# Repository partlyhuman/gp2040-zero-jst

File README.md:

You can quick-order this board at [OSHPark](https://oshpark.com/shared_projects/QktXrqFz).

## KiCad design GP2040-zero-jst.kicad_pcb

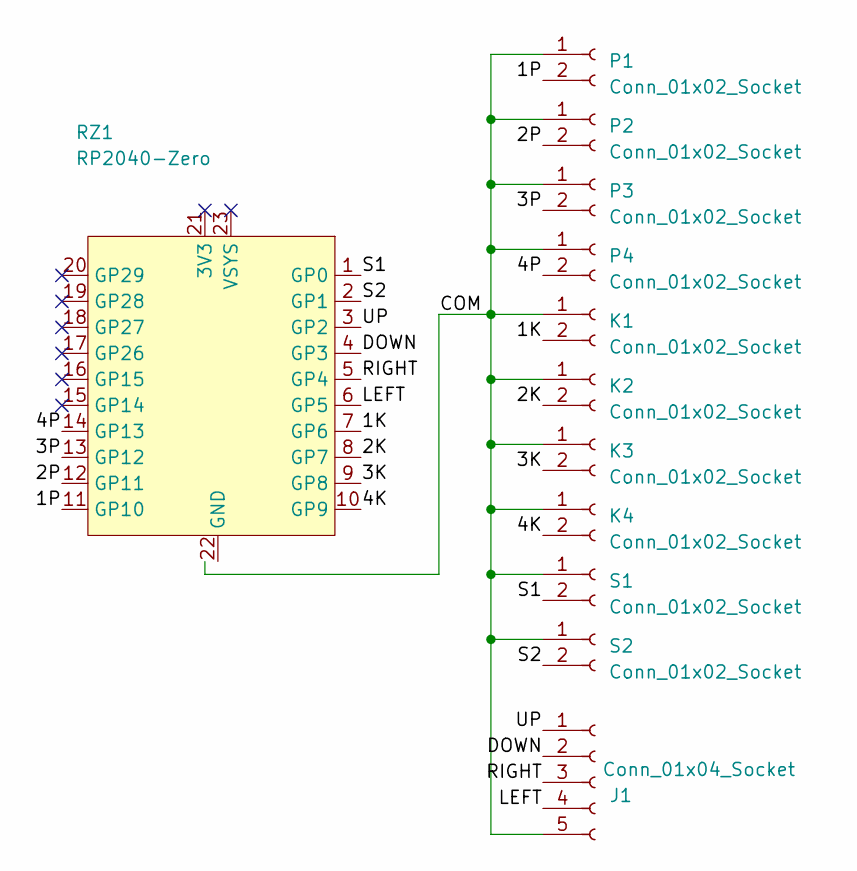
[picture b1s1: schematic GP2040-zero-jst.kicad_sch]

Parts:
J1: Conn_01x04_Socket; JST_XH_B5B-XH-A_1x05_P2.50mm_Vertical
K1, K2, K3, K4: Conn_01x02_Socket; JST_XH_B2B-XH-A_1x02_P2.50mm_Vertical
P1, P2, P3, P4: Conn_01x02_Socket; JST_XH_B2B-XH-A_1x02_P2.50mm_Vertical
RZ1: RP2040-Zero
S1, S2: Conn_01x02_Socket; JST_XH_B2B-XH-A_1x02_P2.50mm_Vertical

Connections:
/1K: K1.2, RZ1.7 (GP6)
/1P: P1.2, RZ1.11 (GP10)
/2K: K2.2, RZ1.8 (GP7)
/2P: P2.2, RZ1.12 (GP11)
/3K: K3.2, RZ1.9 (GP8)
/3P: P3.2, RZ1.13 (GP12)
/4K: K4.2, RZ1.10 (GP9)
/4P: P4.2, RZ1.14 (GP13)
/COM: J1.5, K1.1, K2.1, K3.1, K4.1, P1.1, P2.1, P3.1, P4.1, S1.1, S2.1
/DOWN: J1.2, RZ1.4 (GP3)
/LEFT: J1.4, RZ1.6 (GP5)
/RIGHT: J1.3, RZ1.5 (GP4)
/S1: RZ1.1 (GP0), S1.2
/S2: RZ1.2 (GP1), S2.2
/UP: J1.1, RZ1.3 (GP2)

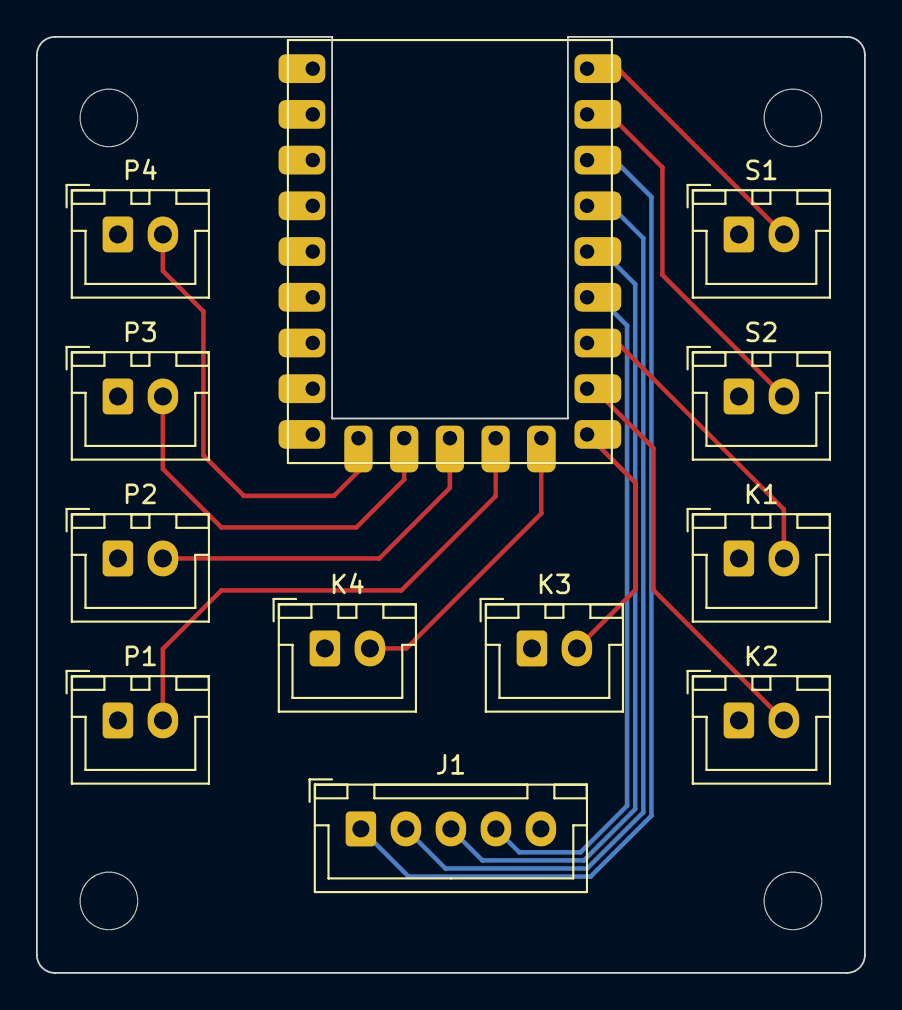
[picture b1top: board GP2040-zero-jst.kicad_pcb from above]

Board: 2 copper layers, 46.0 x 52.0 mm, 12 parts (0 on the bottom side), 15 nets.

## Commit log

2023-03-16 First usable design
2023-03-31 Widen mounting holes, rewire for no-config
2023-03-31 Enlarge gp2040 cutout
